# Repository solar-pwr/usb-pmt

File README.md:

# usb-pmt
USB adapter for gamma scintillation detectors with photomultiplier tubes

## v1.0
### Known bugs
- With 10 MΩ PMT, the power supply can only provide around 600V. Both "on" time and duty cycle need to be higher to get the desired 1500V. This can be achieved by modifying the resistors around U3.
- Filtering capacitance for the low-voltage part of the circuit is too low. This allows noise from the USB power to propagate into the microphone input. There should be at least one 1000 µF capacitor on the power line. However, this does not seem to impact the spectrum quality.
- The green LED glares too much. Higher value of resistor should be used.
- There should be a pole-zero cancellation resistor in parallel to C13, like C10 and R23. 1 kΩ seems to work fine. It improves resolution at lower energies.

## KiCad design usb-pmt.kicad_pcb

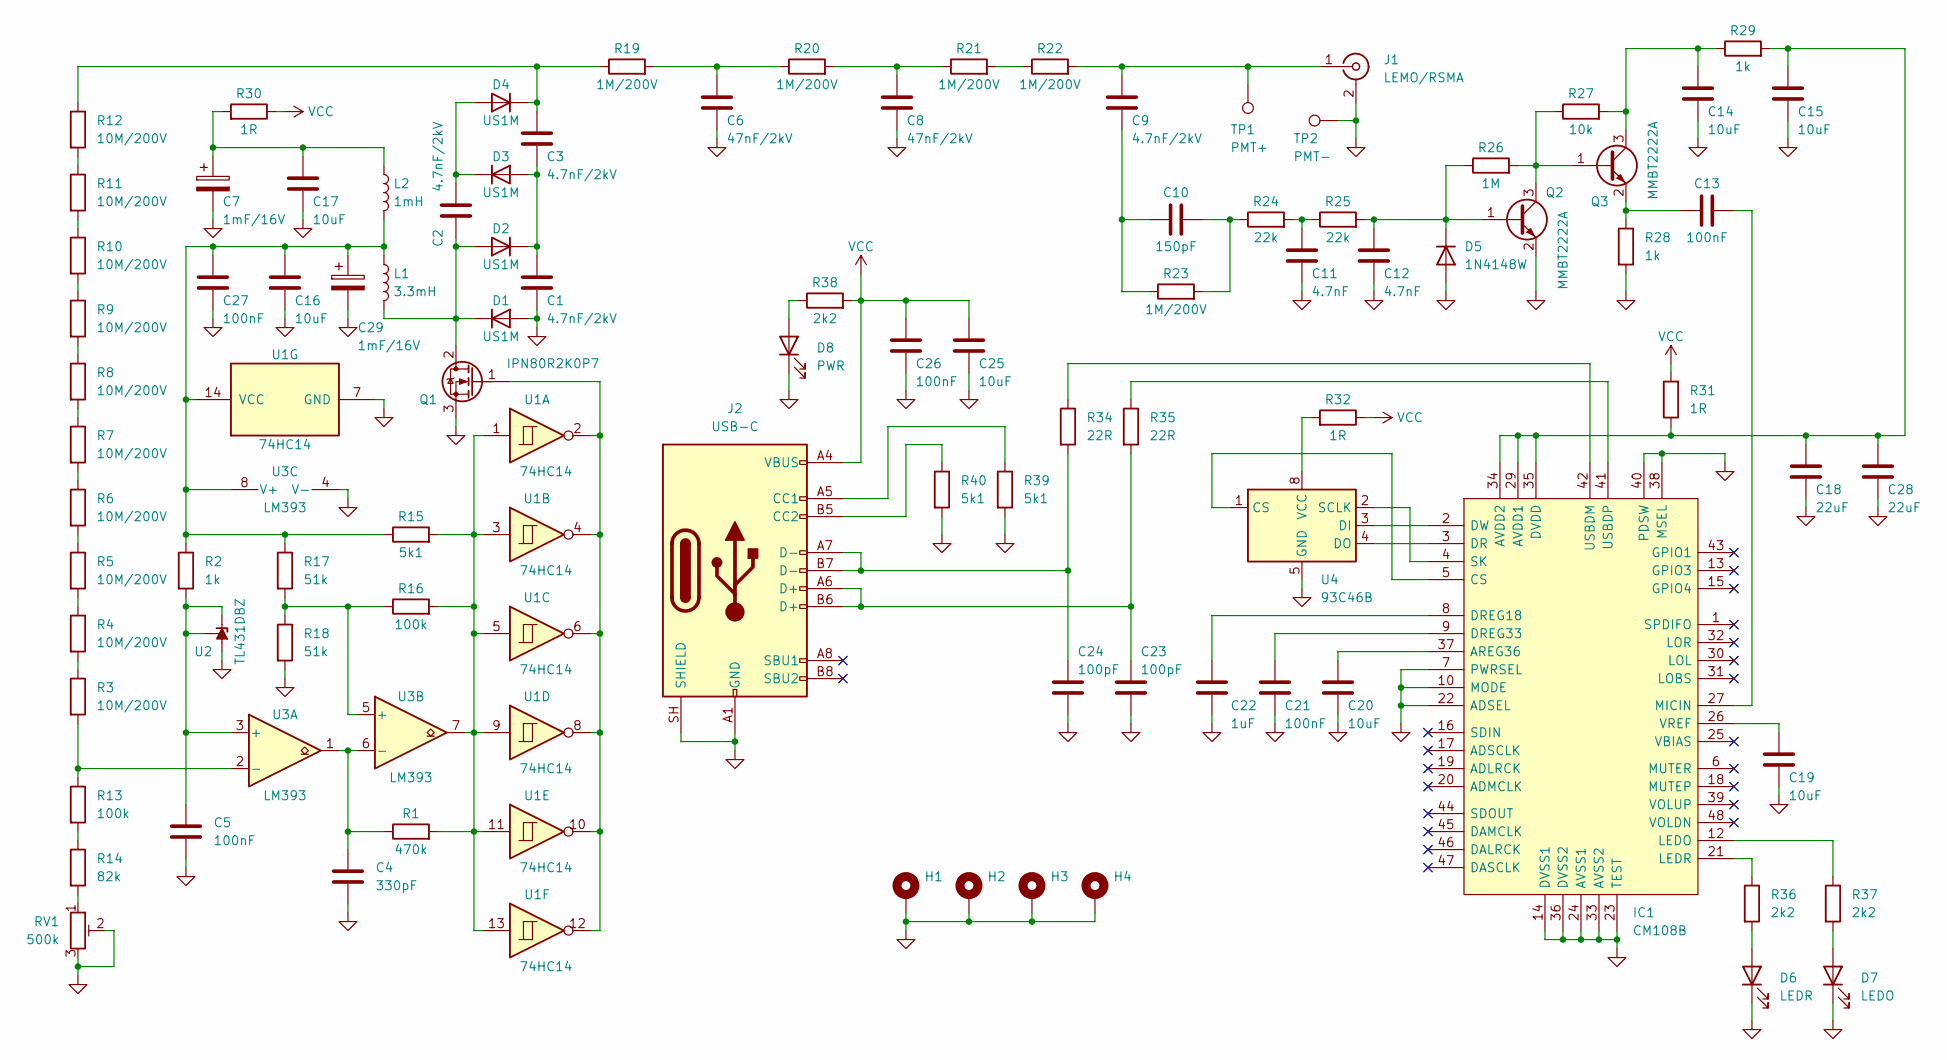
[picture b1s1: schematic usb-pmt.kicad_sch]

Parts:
C1, C2, C3, C9: 4.7nF/2kV; C_1812_4532Metric
C4: 330pF; C_0603_1608Metric
C5: 100nF; C_0603_1608Metric
C6, C8: 47nF/2kV; C_2225_5664Metric
C7, C29: 1mF/16V; CP_Radial_D8.0mm_P3.50mm
C10: 150pF; C_0603_1608Metric
C11, C12: 4.7nF; C_0603_1608Metric
C13, C21, C26, C27: 100nF; C_0805_2012Metric
C14, C15, C16, C17, C20, C25: 10uF; C_0805_2012Metric
C18, C28: 22uF; C_0805_2012Metric; LCSC CL21A226MAQNNNE
C19: 10uF; C_0603_1608Metric
C22: 1uF; C_0805_2012Metric
C23, C24: 100pF; C_0603_1608Metric
D1, D2, D3, D4: US1M; D_SMA
D5: 1N4148W; D_SOD-123
D6: LEDR; LED_0805_2012Metric
D7: LEDO; LED_0805_2012Metric
D8: PWR; LED_0805_2012Metric
H1, H2, H3, H4: MountingHole_Pad; MountingHole_3.2mm_M3_DIN965_Pad
IC1: CM108B; LQFP-48_7x7mm_P0.5mm; Manufacturer_Part_Number CM108
J1: LEMO/RSMA; LEMO-EPL.00.250.NTN+RSMA
J2: USB-C; USB_C_Receptacle_GCT_USB4105-xx-A_16P_TopMnt_Horizontal
L1: 3.3mH; L_Radial_D12.0mm_P5.00mm_Fastron_11P
L2: 1mH; L_Radial_D12.0mm_P5.00mm_Fastron_11P
Q1: IPN80R2K0P7; SOT-223-3_TabPin2
Q2, Q3: MMBT2222A; SOT-23
R1: 470k; R_0603_1608Metric
R2, R28, R29: 1k; R_0603_1608Metric
R3, R4, R5, R6, R7, R8, R9, R10, R11, R12: 10M/200V; R_1206_3216Metric
R13, R16: 100k; R_0603_1608Metric
R14: 82k; R_0603_1608Metric
R15, R39, R40: 5k1; R_0603_1608Metric
R17, R18: 51k; R_0603_1608Metric
R19, R20, R21, R22, R23: 1M/200V; R_1206_3216Metric
R24, R25: 22k; R_0603_1608Metric
R26: 1M; R_0603_1608Metric
R27: 10k; R_0603_1608Metric
R30, R31: 1R; R_1206_3216Metric
R32: 1R; R_0603_1608Metric
R34, R35: 22R; R_0603_1608Metric
R36, R37, R38: 2k2; R_0603_1608Metric
RV1: 500k; Potentiometer_Bourns_3006P_Horizontal
TP1: PMT+; PinHeader_1x01_P2.54mm_Vertical
TP2: PMT-; PinHeader_1x01_P2.54mm_Vertical
U1: 74HC14; SOIC-14_3.9x8.7mm_P1.27mm
U2: TL431DBZ; SOT-23
U3: LM393; SOIC-8_3.9x4.9mm_P1.27mm
U4: 93C46B; DIP-8_W7.62mm_Socket_LongPads

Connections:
GND: C1.1, C4.1, C5.1, C6.1, C7.2, C8.1, C11.2, C12.2, C14.2, C15.2, C16.2, C17.2, C18.2, C19.2, C20.2, C21.2, C22.2, C23.2, C24.2, C25.2, C26.2, C27.2, C28.2, C29.2, D1.2 (A), D5.2 (A), D6.1 (K), D7.1 (K), D8.1 (K), H1.1 (1_1), H2.1 (1_1), H3.1 (1_1), H4.1 (1_1), IC1.7 (PWRSEL), IC1.10 (MODE), IC1.14 (DVSS1), IC1.22 (ADSEL), IC1.23 (TEST), IC1.24 (AVSS1), IC1.33 (AVSS2), IC1.36 (DVSS2), IC1.38 (MSEL), IC1.40 (PDSW), J1.2 (Ext), J2.A1 (GND), J2.A12 (GND), J2.B1 (GND), J2.B12 (GND), J2.SH (SHIELD), Q1.3 (S), Q2.2 (E), R18.2, R28.2, R39.2, R40.2, RV1.2, RV1.3, TP2.1 (1_1), U1.7 (GND), U2.3 (A), U3.4 (V-), U4.5 (GND)
unnamed: C6.2, R19.2, R20.1
unnamed: C8.2, R20.2, R21.1
unnamed: C9.1, C10.1, R23.1
unnamed: C10.2, R23.2, R24.1
unnamed: C11.1, R24.2, R25.1
unnamed: C7.1, C17.1, L2.1, R30.2
unnamed: C23.1, J2.A6 (D+), J2.B6 (D+), R35.2
unnamed: C24.1, J2.A7 (D-), J2.B7 (D-), R34.2
unnamed: C2.1, D1.1 (K), D2.2 (A), L1.2, Q1.2 (D)
unnamed: C1.2, C3.1, D2.1 (K), D3.2 (A)
unnamed: C2.2, D3.1 (K), D4.2 (A)
unnamed: C3.2, D4.1 (K), R12.1, R19.1
unnamed: C12.1, D5.1 (K), Q2.1 (B), R25.2, R26.1
unnamed: D6.2 (A), R36.2
unnamed: D7.2 (A), R37.2
unnamed: D8.2 (A), R38.1
unnamed: C20.1, IC1.37 (AREG36)
unnamed: C15.1, C18.1, C28.1, IC1.29 (AVDD1), IC1.34 (AVDD2), IC1.35 (DVDD), R29.2, R31.1
unnamed: IC1.5 (CS), U4.1 (CS)
unnamed: IC1.3 (DR), U4.4 (DO)
unnamed: C22.1, IC1.8 (DREG18)
unnamed: C21.1, IC1.9 (DREG33)
unnamed: IC1.2 (DW), U4.3 (DI)
unnamed: IC1.12 (LEDO), R37.1
unnamed: IC1.21 (LEDR), R36.1
unnamed: C13.2, IC1.27 (MICIN)
unnamed: IC1.4 (SK), U4.2 (SCLK)
unnamed: IC1.42 (USBDM), R34.1
unnamed: IC1.41 (USBDP), R35.1
unnamed: C19.1, IC1.26 (VREF)
unnamed: C9.2, J1.1 (In), R22.2, TP1.1 (1_1)
unnamed: J2.A5 (CC1), R39.1
unnamed: J2.B5 (CC2), R40.1
unnamed: Q1.1 (G), U1.2, U1.4, U1.6, U1.8, U1.10, U1.12
unnamed: Q2.3 (C), Q3.1 (B), R26.2, R27.1
unnamed: C14.1, Q3.3 (C), R27.2, R29.1
unnamed: C13.1, Q3.2 (E), R28.1
unnamed: R1.2, R15.2, R16.2, U1.1, U1.3, U1.5, U1.9, U1.11, U1.13, U3.7
unnamed: R3.1, R4.2
unnamed: R4.1, R5.2
unnamed: R5.1, R6.2
unnamed: R6.1, R7.2
unnamed: R7.1, R8.2
unnamed: R8.1, R9.2
unnamed: R10.1, R11.2
unnamed: R9.1, R10.2
unnamed: R11.1, R12.2
unnamed: R13.2, R14.1
unnamed: R14.2, RV1.1
unnamed: R21.2, R22.1
unnamed: C16.1, C27.1, C29.1, L1.1, L2.2, R2.1, R15.1, R17.1, U1.14 (VCC), U3.8 (V+)
unnamed: C5.2, R2.2, U2.1 (K), U2.2 (REF), U3.3 (+)
unnamed: R3.2, R13.1, U3.2 (-)
unnamed: R16.1, R17.2, R18.1, U3.5 (+)
unnamed: C4.2, R1.1, U3.1, U3.6 (-)
unnamed: R32.2, U4.8 (VCC)
VCC: C25.1, C26.1, J2.A4 (VBUS), J2.A9 (VBUS), J2.B4 (VBUS), J2.B9 (VBUS), R30.1, R31.2, R32.1, R38.2

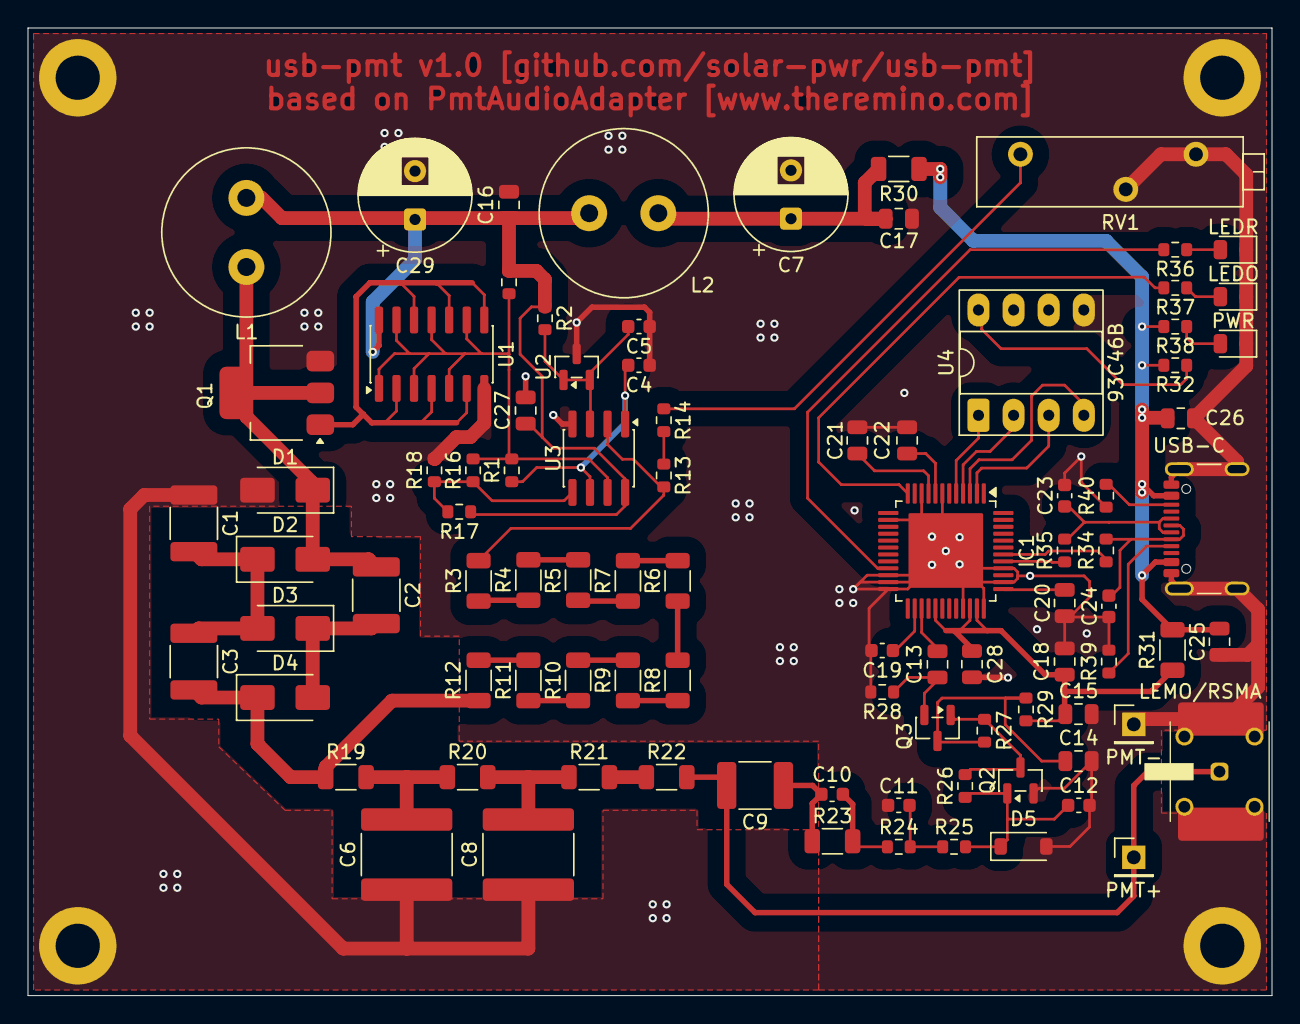
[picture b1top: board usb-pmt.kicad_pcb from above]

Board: 2 copper layers, 90.0 x 70.0 mm, 95 parts (0 on the bottom side), 58 nets.

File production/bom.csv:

Designator,Footprint,Quantity,Value,LCSC Part #
"C1, C2, C3, C9",1812,4,4.7nF/2kV,
C10,0603,1,150pF,
"C11, C12",0603,2,4.7nF,
"C13, C21, C26, C27",0805,4,100nF,
"C14, C15, C16, C17, C20, C25",0805,6,10uF,
"C18, C28",0805,2,22uF,CL21A226MAQNNNE
C19,0603,1,10uF,
C22,0805,1,1uF,
"C23, C24",0603,2,100pF,
"C29, C7",CP_Radial_D8.0mm_P3.50mm,2,1mF/16V,
C4,0603,1,330pF,
C5,0603,1,100nF,
"C6, C8",2225,2,47nF/2kV,
"D1, D2, D3, D4",D_SMA,4,US1M,
D5,D_SOD-123,1,1N4148W,
D6,0805,1,LEDR,
D7,0805,1,LEDO,
D8,0805,1,PWR,
IC1,LQFP-48_7x7mm_P0.5mm,1,CM108B,
J1,LEMO-EPL.00.250.NTN+RSMA,1,LEMO/RSMA,
J2,USB_C_Receptacle_GCT_USB4105-xx-A_16P_TopMnt_Horizontal,1,USB-C,
L1,L_Radial_D12.0mm_P5.00mm_Fastron_11P,1,3.3mH,
L2,L_Radial_D12.0mm_P5.00mm_Fastron_11P,1,1mH,
Q1,SOT-223-3_TabPin2,1,IPN80R2K0P7,
"Q2, Q3",SOT-23,2,MMBT2222A,
R1,0603,1,470k,
"R10, R11, R12, R3, R4, R5, R6, R7, R8, R9",1206,10,10M/200V,
"R13, R16",0603,2,100k,
R14,0603,1,82k,
"R15, R39, R40",0603,3,5k1,
"R17, R18",0603,2,51k,
"R19, R20, R21, R22, R23",1206,5,1M/200V,
"R2, R28, R29",0603,3,1k,
"R24, R25",0603,2,22k,
R26,0603,1,1M,
R27,0603,1,10k,
"R30, R31",1206,2,1R,
R32,0603,1,1R,
"R34, R35",0603,2,22R,
"R36, R37, R38",0603,3,2k2,
RV1,Potentiometer_Bourns_3006P_Horizontal,1,500k,
TP1,PinHeader_1x01_P2.54mm_Vertical,1,PMT+,
TP2,PinHeader_1x01_P2.54mm_Vertical,1,PMT-,
U1,SOIC-14_3.9x8.7mm_P1.27mm,1,74HC14,
U2,SOT-23,1,TL431DBZ,
U3,SOIC-8_3.9x4.9mm_P1.27mm,1,LM393,
U4,DIP-8_W7.62mm_Socket_LongPads,1,93C46B,
